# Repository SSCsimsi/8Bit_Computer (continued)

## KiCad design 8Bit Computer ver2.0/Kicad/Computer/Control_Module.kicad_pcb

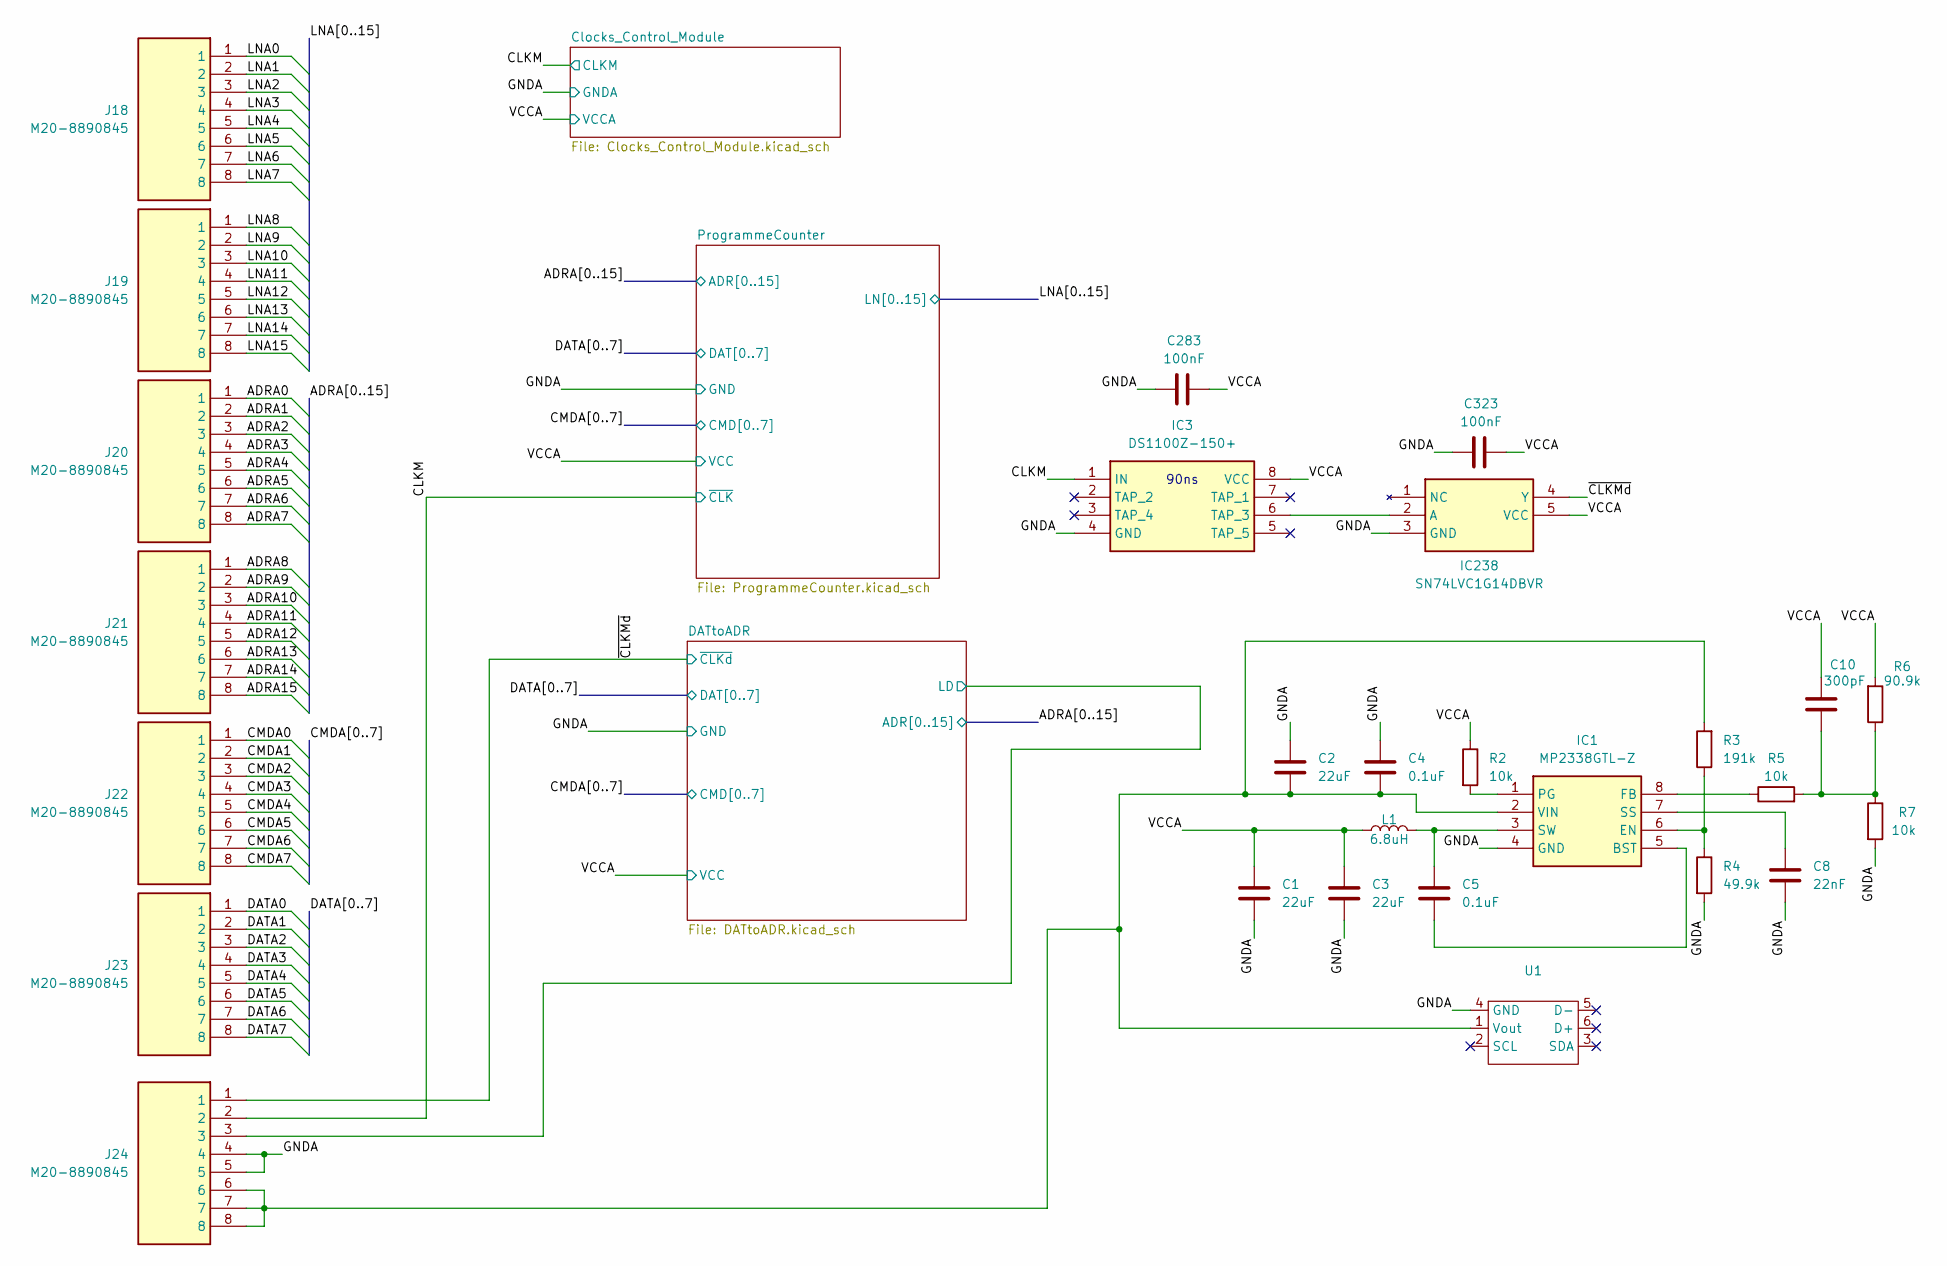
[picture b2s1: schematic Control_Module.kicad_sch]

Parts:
C1, C2, C3: 22uF; C_1206_3216Metric_Pad1.33x1.80mm_HandSolder
C4, C5: 0.1uF; C_1206_3216Metric_Pad1.33x1.80mm_HandSolder
C8: 22nF; C_1206_3216Metric_Pad1.33x1.80mm_HandSolder
C10: 300pF; C_1206_3216Metric_Pad1.33x1.80mm_HandSolder
C283, C323: 100nF; C_1206_3216Metric_Pad1.33x1.80mm_HandSolder
IC1: MP2338GTL-Z; MP2338GTLZ; Mouser Part Number 946-MP2338GTL-Z
IC3: DS1100Z-150+; SOIC127P600X175-8N; Mouser Part Number 700-DS1100Z-150
IC238: SN74LVC1G14DBVR; SOT95P280X145-5N; Mouser Part Number 595-SN74LVC1G14DBVR
J18, J19, J20, J21, J22, J23, J24: M20-8890845; M208890845; Mouser Part Number 855-M20-8890845
L1: 6.8uH; INDPM108100X400N; Mouser Part Number 80-MPEV1D1040L6R8
R2, R5, R7: 10k; R_1206_3216Metric_Pad1.30x1.75mm_HandSolder
R3: 191k; R_1206_3216Metric_Pad1.30x1.75mm_HandSolder
R4: 49.9k; R_1206_3216Metric_Pad1.30x1.75mm_HandSolder
R6: 90.9k; R_1206_3216Metric_Pad1.30x1.75mm_HandSolder
U1: USB_C_PD_Triggerboard

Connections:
/ADRA0: J20.1; also elsewhere on the board
/ADRA1: J20.2; also elsewhere on the board
/ADRA2: J20.3; also elsewhere on the board
/ADRA3: J20.4; also elsewhere on the board
/ADRA4: J20.5; also elsewhere on the board
/ADRA5: J20.6; also elsewhere on the board
/ADRA6: J20.7; also elsewhere on the board
/ADRA7: J20.8; also elsewhere on the board
/ADRA8: J21.1; also elsewhere on the board
/ADRA9: J21.2; also elsewhere on the board
/ADRA10: J21.3; also elsewhere on the board
/ADRA11: J21.4; also elsewhere on the board
/ADRA12: J21.5; also elsewhere on the board
/ADRA13: J21.6; also elsewhere on the board
/ADRA14: J21.7; also elsewhere on the board
/ADRA15: J21.8; also elsewhere on the board
/CMDA0: J22.1; also elsewhere on the board
/CMDA1: J22.2; also elsewhere on the board
/CMDA2: J22.3; also elsewhere on the board
/CMDA3: J22.4; also elsewhere on the board
/CMDA4: J22.5; also elsewhere on the board
/CMDA5: J22.6; also elsewhere on the board
/CMDA6: J22.7; also elsewhere on the board
/CMDA7: J22.8; also elsewhere on the board
/DATA0: J23.1; also elsewhere on the board
/DATA1: J23.2; also elsewhere on the board
/DATA2: J23.3; also elsewhere on the board
/DATA3: J23.4; also elsewhere on the board
/DATA4: J23.5; also elsewhere on the board
/DATA5: J23.6; also elsewhere on the board
/DATA6: J23.7; also elsewhere on the board
/DATA7: J23.8; also elsewhere on the board
/DATtoADR/LD: J24.3; also elsewhere on the board
/DATtoADR/~CLKd: IC3.6 (TAP_3), IC238.2 (A), IC238.4 (Y), J24.1; also elsewhere on the board
/GNDA: C1.2, C2.1, C3.2, C4.1, C8.2, C283.2, C323.2, IC1.4 (GND), IC3.4 (GND), IC238.3 (GND), J24.4, J24.5, R4.2, R7.2, U1.4 (GND); also elsewhere on the board
/LNA0: J18.1; also elsewhere on the board
/LNA1: J18.2; also elsewhere on the board
/LNA2: J18.3; also elsewhere on the board
/LNA3: J18.4; also elsewhere on the board
/LNA4: J18.5; also elsewhere on the board
/LNA5: J18.6; also elsewhere on the board
/LNA6: J18.7; also elsewhere on the board
/LNA7: J18.8; also elsewhere on the board
/LNA8: J19.1; also elsewhere on the board
/LNA9: J19.2; also elsewhere on the board
/LNA10: J19.3; also elsewhere on the board
/LNA11: J19.4; also elsewhere on the board
/LNA12: J19.5; also elsewhere on the board
/LNA13: J19.6; also elsewhere on the board
/LNA14: J19.7; also elsewhere on the board
/LNA15: J19.8; also elsewhere on the board
/ProgrammeCounter/~CLK: IC3.1 (IN), J24.2; also elsewhere on the board
/VCCA: C1.1, C3.1, C10.1, C283.1, C323.1, IC3.8 (VCC), IC238.5 (VCC), L1.1, R2.1, R6.2; also elsewhere on the board
unnamed: C10.2, R5.2, R6.1, R7.1
unnamed: C5.2, IC1.5 (BST)
unnamed: IC1.6 (EN), R3.1, R4.1
unnamed: IC1.8 (FB), R5.1
unnamed: IC1.1 (PG), R2.2
unnamed: C8.1, IC1.7 (SS)
unnamed: C5.1, IC1.3 (SW), L1.2
unnamed: C2.2, C4.2, IC1.2 (VIN), J24.6, J24.7, J24.8, R3.2, U1.1 (Vout)

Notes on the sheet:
90ns

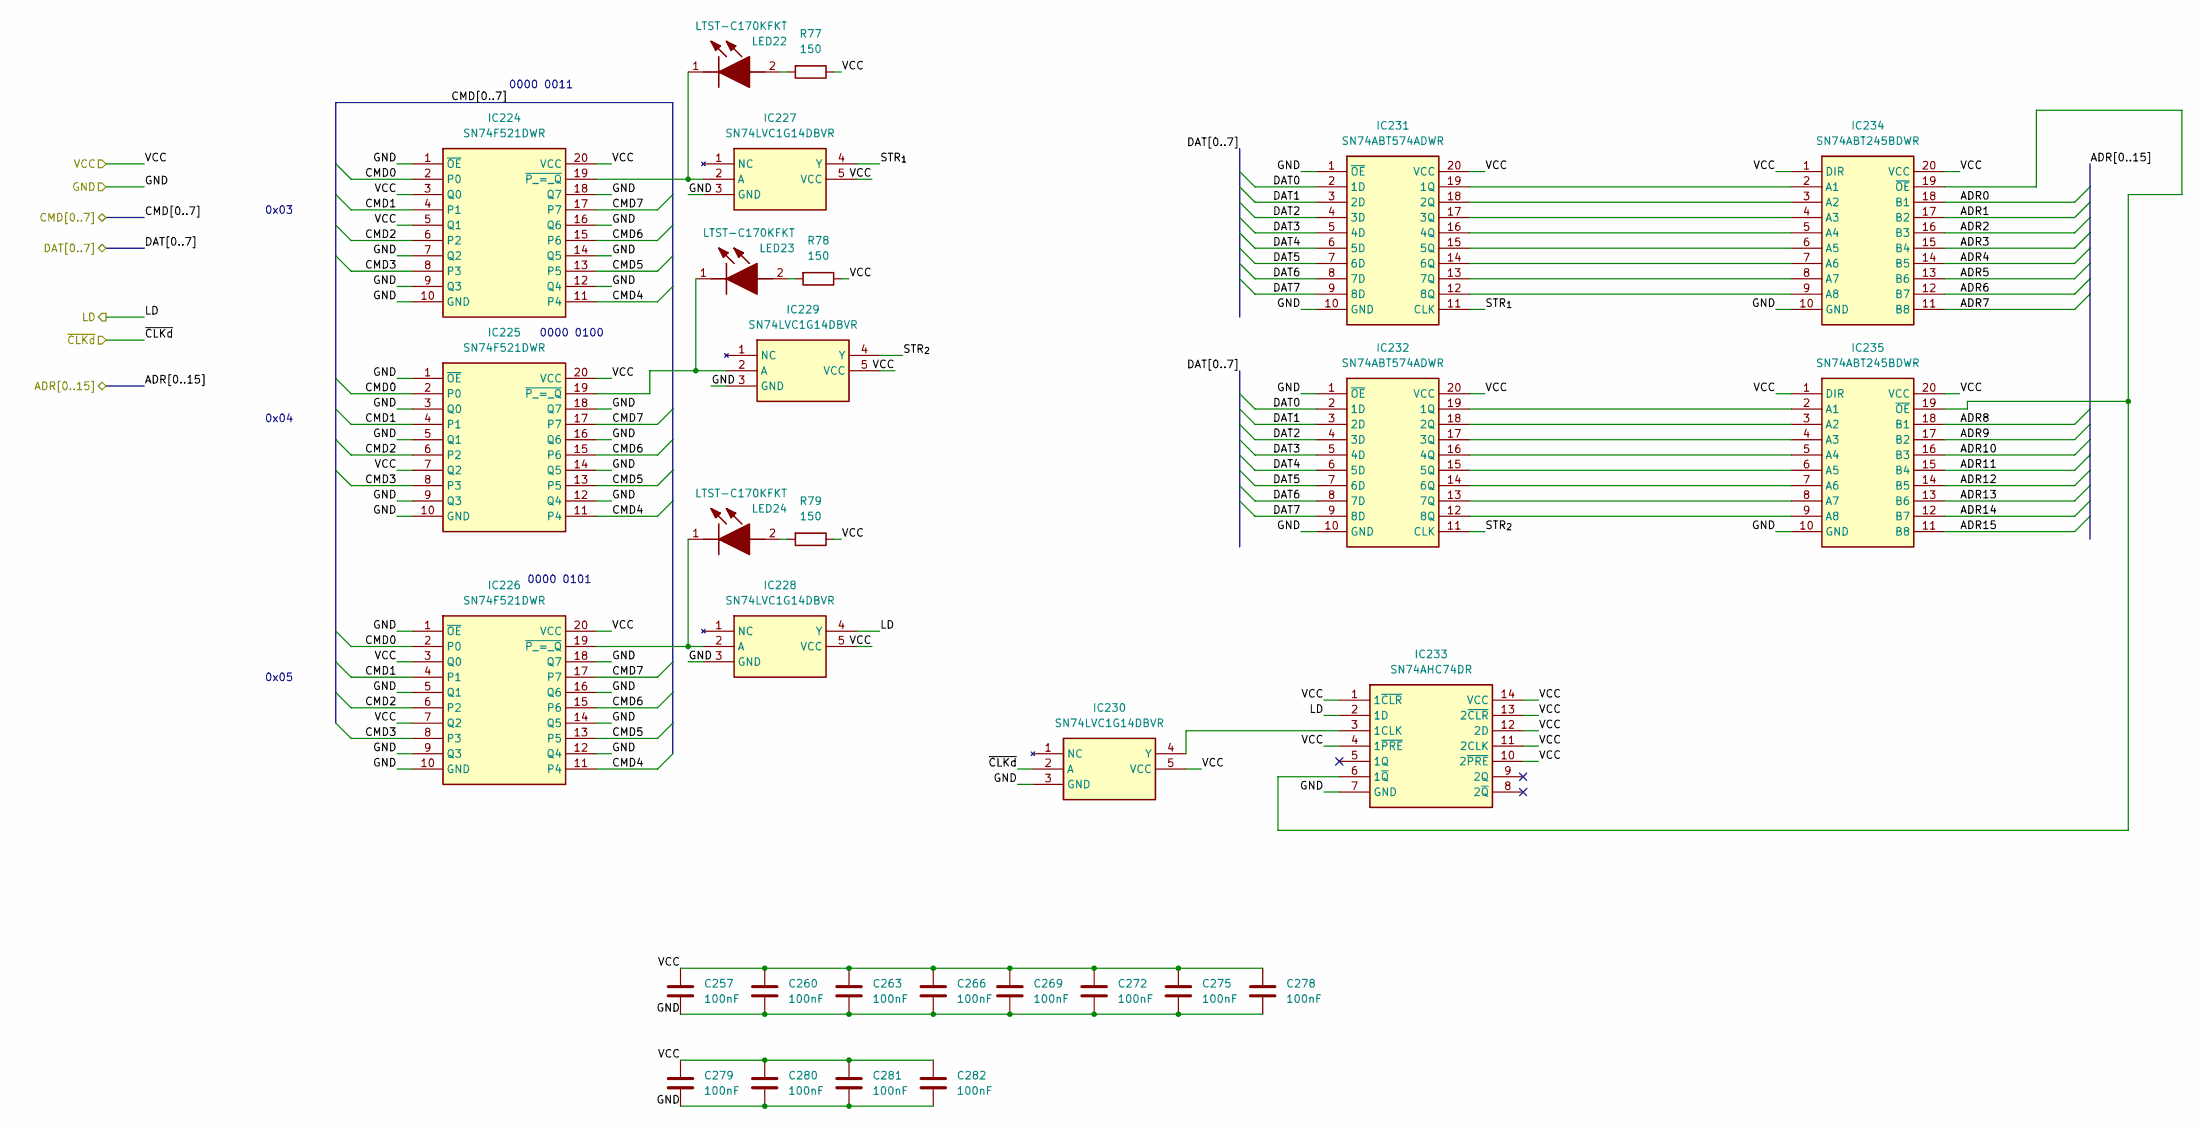
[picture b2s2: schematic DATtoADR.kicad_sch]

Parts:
C257, C260, C263, C266, C269, C272, C275, C278, C279, C280, C281, C282: 100nF; C_1206_3216Metric_Pad1.33x1.80mm_HandSolder
IC224, IC225, IC226: SN74F521DWR; SOIC127P1030X265-20N; Mouser Part Number 595-SN74F521DWR
IC227, IC228, IC229, IC230: SN74LVC1G14DBVR; SOT95P280X145-5N; Mouser Part Number 595-SN74LVC1G14DBVR
IC231, IC232: SN74ABT574ADWR; SOIC127P1030X265-20N; Mouser Part Number 595-SN74ABT574ADWR
IC233: SN74AHC74DR; SOIC127P600X175-14N; Mouser Part Number 595-SN74AHC74DR
IC234, IC235: SN74ABT245BDWR; SOIC127P1030X265-20N; Mouser Part Number 595-SN74ABT245BDWR
LED22, LED23, LED24: LTST-C170KFKT; LEDC2012X120N; Mouser Part Number 859-LTST-C170KFKT
R77, R78, R79: 150; R_1206_3216Metric_Pad1.30x1.75mm_HandSolder

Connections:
/ADRA0: IC234.18 (B1); also elsewhere on the board
/ADRA1: IC234.17 (B2); also elsewhere on the board
/ADRA2: IC234.16 (B3); also elsewhere on the board
/ADRA3: IC234.15 (B4); also elsewhere on the board
/ADRA4: IC234.14 (B5); also elsewhere on the board
/ADRA5: IC234.13 (B6); also elsewhere on the board
/ADRA6: IC234.12 (B7); also elsewhere on the board
/ADRA7: IC234.11 (B8); also elsewhere on the board
/ADRA8: IC235.18 (B1); also elsewhere on the board
/ADRA9: IC235.17 (B2); also elsewhere on the board
/ADRA10: IC235.16 (B3); also elsewhere on the board
/ADRA11: IC235.15 (B4); also elsewhere on the board
/ADRA12: IC235.14 (B5); also elsewhere on the board
/ADRA13: IC235.13 (B6); also elsewhere on the board
/ADRA14: IC235.12 (B7); also elsewhere on the board
/ADRA15: IC235.11 (B8); also elsewhere on the board
/CMDA0: IC224.2 (P0), IC225.2 (P0), IC226.2 (P0); also elsewhere on the board
/CMDA1: IC224.4 (P1), IC225.4 (P1), IC226.4 (P1); also elsewhere on the board
/CMDA2: IC224.6 (P2), IC225.6 (P2), IC226.6 (P2); also elsewhere on the board
/CMDA3: IC224.8 (P3), IC225.8 (P3), IC226.8 (P3); also elsewhere on the board
/CMDA4: IC224.11 (P4), IC225.11 (P4), IC226.11 (P4); also elsewhere on the board
/CMDA5: IC224.13 (P5), IC225.13 (P5), IC226.13 (P5); also elsewhere on the board
/CMDA6: IC224.15 (P6), IC225.15 (P6), IC226.15 (P6); also elsewhere on the board
/CMDA7: IC224.17 (P7), IC225.17 (P7), IC226.17 (P7); also elsewhere on the board
/DATA0: IC231.2 (1D), IC232.2 (1D); also elsewhere on the board
/DATA1: IC231.3 (2D), IC232.3 (2D); also elsewhere on the board
/DATA2: IC231.4 (3D), IC232.4 (3D); also elsewhere on the board
/DATA3: IC231.5 (4D), IC232.5 (4D); also elsewhere on the board
/DATA4: IC231.6 (5D), IC232.6 (5D); also elsewhere on the board
/DATA5: IC231.7 (6D), IC232.7 (6D); also elsewhere on the board
/DATA6: IC231.8 (7D), IC232.8 (7D); also elsewhere on the board
/DATA7: IC231.9 (8D), IC232.9 (8D); also elsewhere on the board
/DATtoADR/LD: IC228.4 (Y), IC233.2 (1D); also elsewhere on the board
/DATtoADR/STR_{1}: IC227.4 (Y), IC231.11 (CLK)
/DATtoADR/STR_{2}: IC229.4 (Y), IC232.11 (CLK)
/DATtoADR/~CLKd: IC230.2 (A); also elsewhere on the board
/GNDA: C257.1, C260.1, C263.1, C266.1, C269.1, C272.1, C275.1, C278.1, C279.1, C280.1, C281.1, C282.1, IC224.1 (~OE), IC224.7 (Q2), IC224.9 (Q3), IC224.10 (GND), IC224.12 (Q4), IC224.14 (Q5), IC224.16 (Q6), IC224.18 (Q7), IC225.1 (~OE), IC225.3 (Q0), IC225.5 (Q1), IC225.9 (Q3), IC225.10 (GND), IC225.12 (Q4), IC225.14 (Q5), IC225.16 (Q6), IC225.18 (Q7), IC226.1 (~OE), IC226.5 (Q1), IC226.9 (Q3), IC226.10 (GND), IC226.12 (Q4), IC226.14 (Q5), IC226.16 (Q6), IC226.18 (Q7), IC227.3 (GND), IC228.3 (GND), IC229.3 (GND), IC230.3 (GND), IC231.1 (~OE), IC231.10 (GND), IC232.1 (~OE), IC232.10 (GND), IC233.7 (GND), IC234.10 (GND), IC235.10 (GND); also elsewhere on the board
/VCCA: C257.2, C260.2, C263.2, C266.2, C269.2, C272.2, C275.2, C278.2, C279.2, C280.2, C281.2, C282.2, IC224.3 (Q0), IC224.5 (Q1), IC224.20 (VCC), IC225.7 (Q2), IC225.20 (VCC), IC226.3 (Q0), IC226.7 (Q2), IC226.20 (VCC), IC227.5 (VCC), IC228.5 (VCC), IC229.5 (VCC), IC230.5 (VCC), IC231.20 (VCC), IC232.20 (VCC), IC233.1 (1~CLR), IC233.4 (1~PRE), IC233.10 (2~PRE), IC233.11 (2CLK), IC233.12 (2D), IC233.13 (2~CLR), IC233.14 (VCC), IC234.1 (DIR), IC234.20 (VCC), IC235.1 (DIR), IC235.20 (VCC), R77.1, R78.1, R79.1; also elsewhere on the board
unnamed: IC224.19 (~P_=_Q), IC227.2 (A), LED22.1 (K)
unnamed: IC225.19 (~P_=_Q), IC229.2 (A), LED23.1 (K)
unnamed: IC226.19 (~P_=_Q), IC228.2 (A), LED24.1 (K)
unnamed: IC230.4 (Y), IC233.3 (1CLK)
unnamed: IC231.19 (1Q), IC234.2 (A1)
unnamed: IC231.18 (2Q), IC234.3 (A2)
unnamed: IC231.17 (3Q), IC234.4 (A3)
unnamed: IC231.16 (4Q), IC234.5 (A4)
unnamed: IC231.15 (5Q), IC234.6 (A5)
unnamed: IC231.14 (6Q), IC234.7 (A6)
unnamed: IC231.13 (7Q), IC234.8 (A7)
unnamed: IC231.12 (8Q), IC234.9 (A8)
unnamed: IC232.19 (1Q), IC235.2 (A1)
unnamed: IC232.18 (2Q), IC235.3 (A2)
unnamed: IC232.17 (3Q), IC235.4 (A3)
unnamed: IC232.16 (4Q), IC235.5 (A4)
unnamed: IC232.15 (5Q), IC235.6 (A5)
unnamed: IC232.14 (6Q), IC235.7 (A6)
unnamed: IC232.13 (7Q), IC235.8 (A7)
unnamed: IC232.12 (8Q), IC235.9 (A8)
unnamed: IC233.6 (1~Q), IC234.19 (~OE), IC235.19 (~OE)
unnamed: LED22.2 (A), R77.2
unnamed: LED23.2 (A), R78.2
unnamed: LED24.2 (A), R79.2

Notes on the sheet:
0000 0011
0000 0100
0x04
0x05
0000 0101
0x03

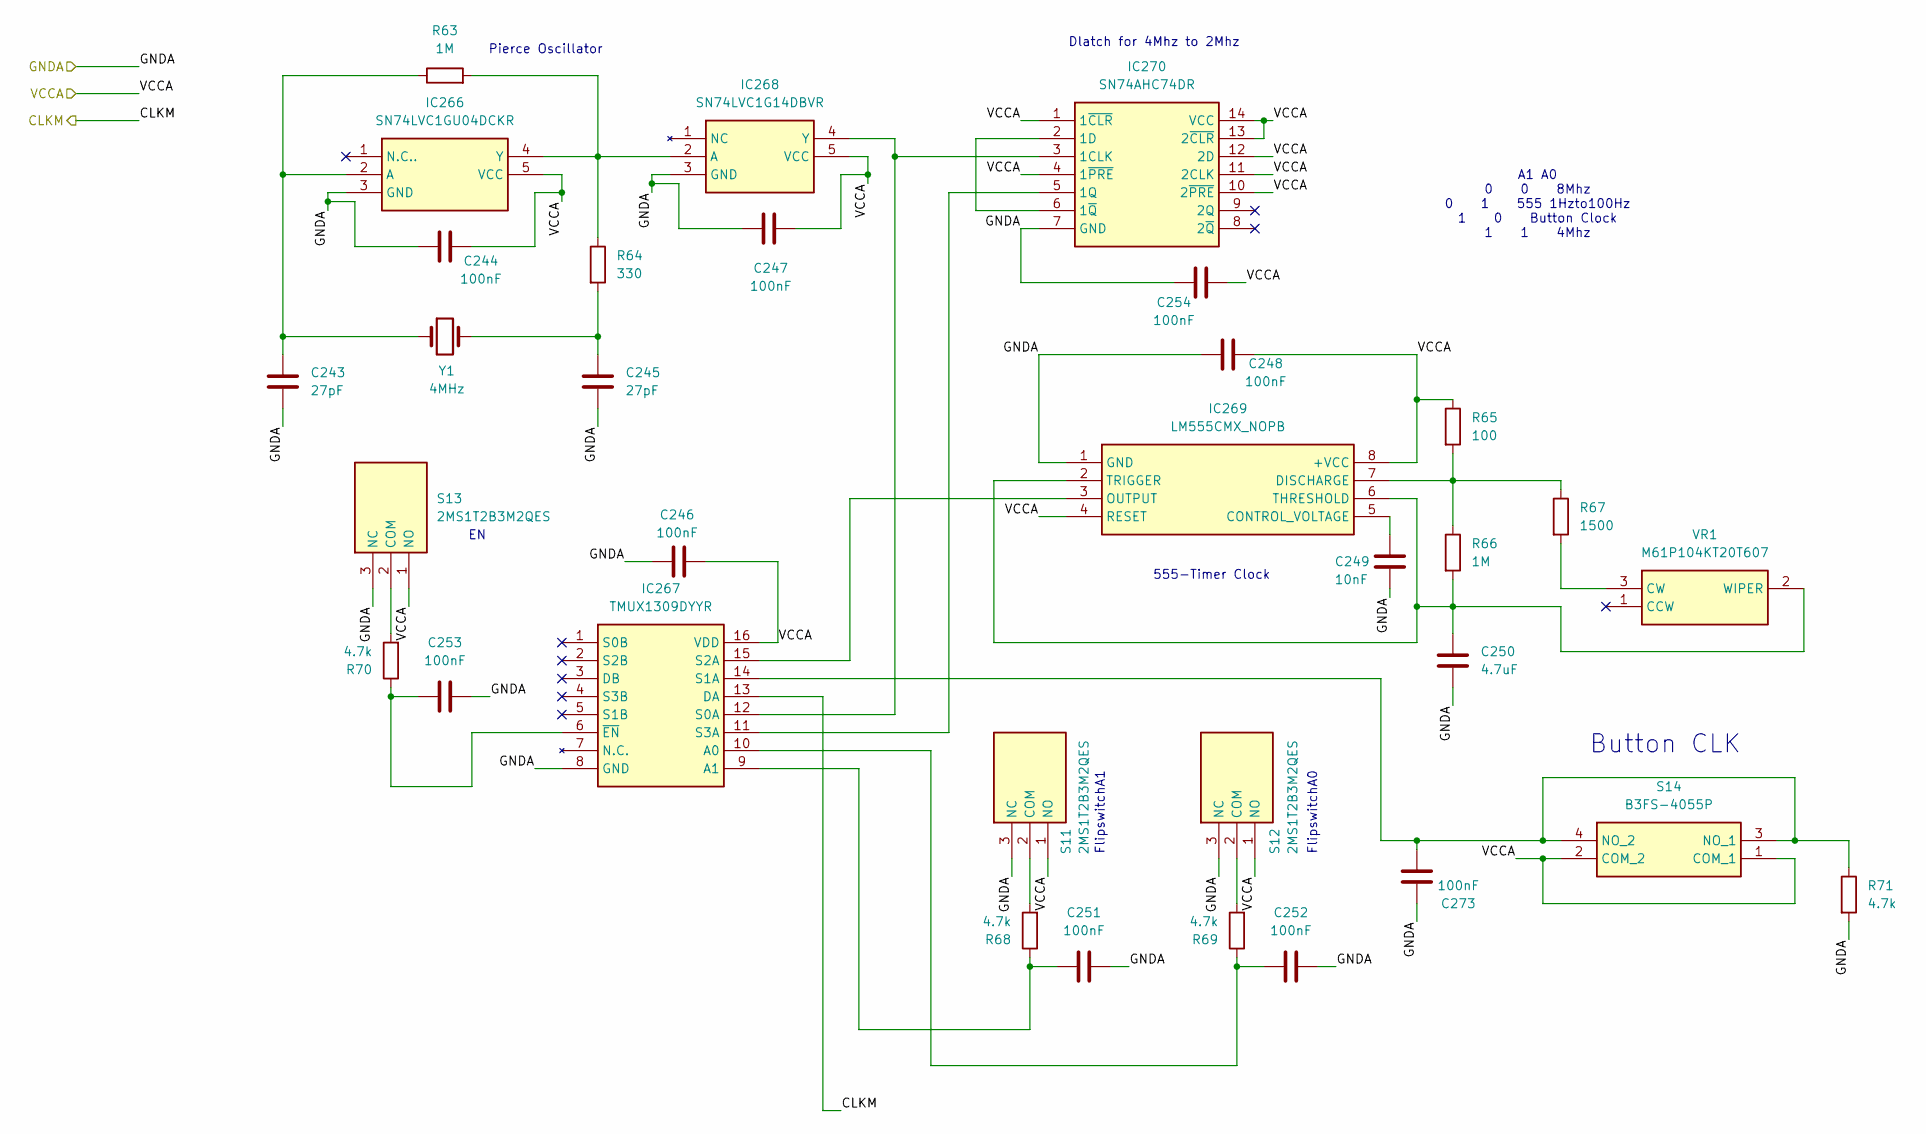
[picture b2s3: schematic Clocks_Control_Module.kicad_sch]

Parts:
C243, C245: 27pF; C_1206_3216Metric_Pad1.33x1.80mm_HandSolder
C244, C246, C247, C248, C251, C252, C253, C254, C273: 100nF; C_1206_3216Metric_Pad1.33x1.80mm_HandSolder
C249: 10nF; C_1206_3216Metric_Pad1.33x1.80mm_HandSolder
C250: 4.7uF; C_1206_3216Metric_Pad1.33x1.80mm_HandSolder
IC266: SN74LVC1GU04DCKR; SOT65P210X110-5N; Mouser Part Number 595-SN74LVC1GU04DCKR
IC267: TMUX1309DYYR; SOP50P326X110-16N; Mouser Part Number 595-TMUX1309DYYR
IC268: SN74LVC1G14DBVR; SOT95P280X145-5N; Mouser Part Number 595-SN74LVC1G14DBVR
IC269: LM555CMX_NOPB; SOIC127P600X175-8N; Mouser Part Number 926-LM555CMX/NOPB
IC270: SN74AHC74DR; SOIC127P600X175-14N; Mouser Part Number 595-SN74AHC74DR
R63, R66: 1M; R_1206_3216Metric_Pad1.30x1.75mm_HandSolder
R64: 330; R_1206_3216Metric_Pad1.30x1.75mm_HandSolder
R65: 100; R_1206_3216Metric_Pad1.30x1.75mm_HandSolder
R67: 1500; R_1206_3216Metric_Pad1.30x1.75mm_HandSolder
R68, R69, R70, R71: 4.7k; R_1206_3216Metric_Pad1.30x1.75mm_HandSolder
S11, S12, S13: 2MS1T2B3M2QES; Mouser Part Number 118-2MS1T2B3M2QES
S14: B3FS-4055P; B3FS4055P; Mouser Part Number 653-B3FS-4055P
VR1: M61P104KT20T607; Manufacturer_Part_Number M61P104KT20T607
Y1: 4MHz; Crystal_SMD_HC49-SD_HandSoldering

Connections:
/GNDA: C243.2, C244.2, C245.2, C246.2, C247.2, C248.2, C249.2, C250.2, C251.1, C252.1, C253.1, C254.2, C273.1, IC266.3 (GND), IC267.8 (GND), IC268.3 (GND), IC269.1 (GND), IC270.7 (GND), R71.2, S11.3 (NC), S12.3 (NC), S13.3 (NC); also elsewhere on the board
/ProgrammeCounter/~CLK: IC267.13 (DA); also elsewhere on the board
/VCCA: C244.1, C246.1, C247.1, C248.1, C254.1, IC266.5 (VCC), IC267.16 (VDD), IC268.5 (VCC), IC269.4 (RESET), IC269.8 (+VCC), IC270.1 (1~CLR), IC270.4 (1~PRE), IC270.10 (2~PRE), IC270.11 (2CLK), IC270.12 (2D), IC270.13 (2~CLR), IC270.14 (VCC), R65.1, S11.1 (NO), S12.1 (NO), S13.1 (NO), S14.1 (COM_1), S14.2 (COM_2); also elsewhere on the board
unnamed: C245.1, R64.2, Y1.2
unnamed: C243.1, IC266.2 (A), R63.1, Y1.1
unnamed: IC266.4 (Y), IC268.2 (A), R63.2, R64.1
unnamed: C252.2, IC267.10 (A0), R69.1
unnamed: C251.2, IC267.9 (A1), R68.1
unnamed: IC267.12 (S0A), IC268.4 (Y), IC270.3 (1CLK)
unnamed: C273.2, IC267.14 (S1A), R71.1, S14.3 (NO_1), S14.4 (NO_2)
unnamed: IC267.15 (S2A), IC269.3 (OUTPUT)
unnamed: IC267.11 (S3A), IC270.5 (1Q)
unnamed: C253.2, IC267.6 (~EN), R70.1
unnamed: C249.1, IC269.5 (CONTROL_VOLTAGE)
unnamed: IC269.7 (DISCHARGE), R65.2, R66.1, R67.1
unnamed: C250.1, IC269.2 (TRIGGER), IC269.6 (THRESHOLD), R66.2, VR1.2 (WIPER)
unnamed: IC270.2 (1D), IC270.6 (1~Q)
unnamed: R68.2, S11.2 (COM)
unnamed: R69.2, S12.2 (COM)
unnamed: R70.2, S13.2 (COM)
unnamed: R67.2, VR1.3 (CW)

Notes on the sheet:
Pierce Oscillator
Dlatch for 4Mhz to 2Mhz
555-Timer Clock
A1 A0 0 0 8Mhz 0 1 555 1Hzto100Hz 1 0 Button Clock 1 1 4Mhz
FlipswitchA1
Button CLK
FlipswitchA0

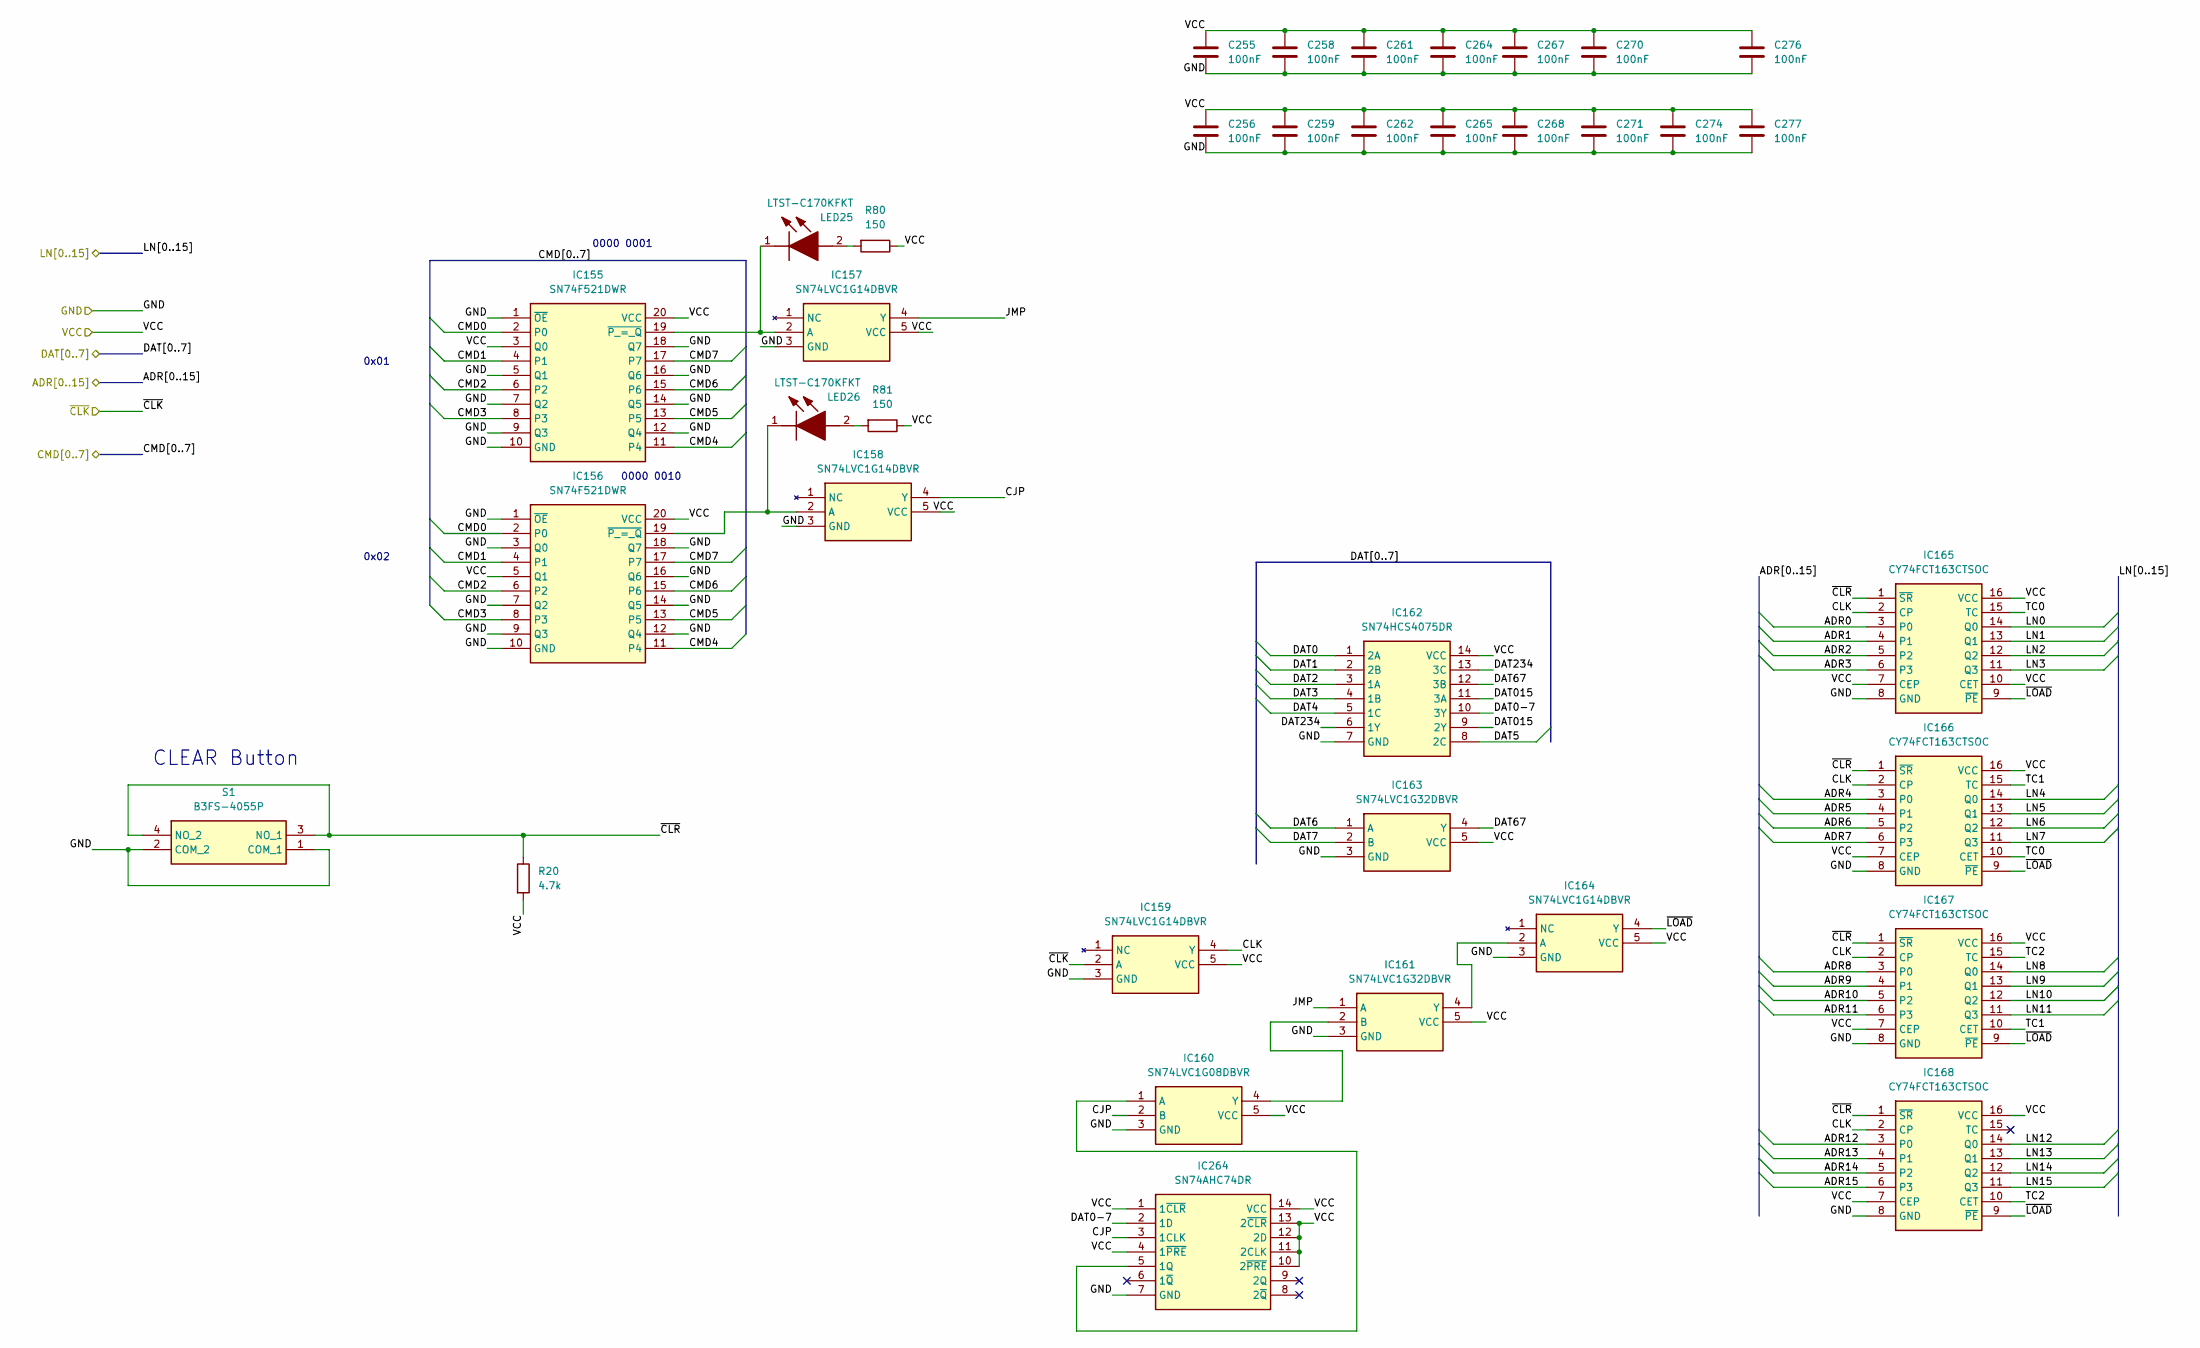
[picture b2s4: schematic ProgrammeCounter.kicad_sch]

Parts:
C255, C256, C258, C259, C261, C262, C264, C265, C267, C268, C270, C271, C274, C276, C277: 100nF; C_1206_3216Metric_Pad1.33x1.80mm_HandSolder
IC155, IC156: SN74F521DWR; SOIC127P1030X265-20N; Mouser Part Number 595-SN74F521DWR
IC157, IC158, IC159, IC164: SN74LVC1G14DBVR; SOT95P280X145-5N; Mouser Part Number 595-SN74LVC1G14DBVR
IC160: SN74LVC1G08DBVR; SOT95P280X145-5N; Mouser Part Number 595-SN74LVC1G08DBVR
IC161, IC163: SN74LVC1G32DBVR; SOT95P280X145-5N; Mouser Part Number 595-SN74LVC1G32DBVR
IC162: SN74HCS4075DR; SOIC127P600X175-14N; Mouser Part Number 595-SN74HCS4075DR
IC165, IC166, IC167, IC168: CY74FCT163CTSOC; SOIC127P1030X265-16N; Mouser Part Number 595-CY74FCT163CTSOC
IC264: SN74AHC74DR; SOIC127P600X175-14N; Mouser Part Number 595-SN74AHC74DR
LED25, LED26: LTST-C170KFKT; LEDC2012X120N; Mouser Part Number 859-LTST-C170KFKT
R20: 4.7k; R_1206_3216Metric_Pad1.30x1.75mm_HandSolder
R80, R81: 150; R_1206_3216Metric_Pad1.30x1.75mm_HandSolder
S1: B3FS-4055P; B3FS4055P; Mouser Part Number 653-B3FS-4055P

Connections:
/ADRA0: IC165.3 (P0); also elsewhere on the board
/ADRA1: IC165.4 (P1); also elsewhere on the board
/ADRA2: IC165.5 (P2); also elsewhere on the board
/ADRA3: IC165.6 (P3); also elsewhere on the board
/ADRA4: IC166.3 (P0); also elsewhere on the board
/ADRA5: IC166.4 (P1); also elsewhere on the board
/ADRA6: IC166.5 (P2); also elsewhere on the board
/ADRA7: IC166.6 (P3); also elsewhere on the board
/ADRA8: IC167.3 (P0); also elsewhere on the board
/ADRA9: IC167.4 (P1); also elsewhere on the board
/ADRA10: IC167.5 (P2); also elsewhere on the board
/ADRA11: IC167.6 (P3); also elsewhere on the board
/ADRA12: IC168.3 (P0); also elsewhere on the board
/ADRA13: IC168.4 (P1); also elsewhere on the board
/ADRA14: IC168.5 (P2); also elsewhere on the board
/ADRA15: IC168.6 (P3); also elsewhere on the board
/CMDA0: IC155.2 (P0), IC156.2 (P0); also elsewhere on the board
/CMDA1: IC155.4 (P1), IC156.4 (P1); also elsewhere on the board
/CMDA2: IC155.6 (P2), IC156.6 (P2); also elsewhere on the board
/CMDA3: IC155.8 (P3), IC156.8 (P3); also elsewhere on the board
/CMDA4: IC155.11 (P4), IC156.11 (P4); also elsewhere on the board
/CMDA5: IC155.13 (P5), IC156.13 (P5); also elsewhere on the board
/CMDA6: IC155.15 (P6), IC156.15 (P6); also elsewhere on the board
/CMDA7: IC155.17 (P7), IC156.17 (P7); also elsewhere on the board
/DATA0: IC162.1 (2A); also elsewhere on the board
/DATA1: IC162.2 (2B); also elsewhere on the board
/DATA2: IC162.3 (1A); also elsewhere on the board
/DATA3: IC162.4 (1B); also elsewhere on the board
/DATA4: IC162.5 (1C); also elsewhere on the board
/DATA5: IC162.8 (2C); also elsewhere on the board
/DATA6: IC163.1 (A); also elsewhere on the board
/DATA7: IC163.2 (B); also elsewhere on the board
/GNDA: C255.1, C256.1, C258.1, C259.1, C261.1, C262.1, C264.1, C265.1, C267.1, C268.1, C270.1, C271.1, C274.1, C276.1, C277.1, IC155.1 (~OE), IC155.5 (Q1), IC155.7 (Q2), IC155.9 (Q3), IC155.10 (GND), IC155.12 (Q4), IC155.14 (Q5), IC155.16 (Q6), IC155.18 (Q7), IC156.1 (~OE), IC156.3 (Q0), IC156.7 (Q2), IC156.9 (Q3), IC156.10 (GND), IC156.12 (Q4), IC156.14 (Q5), IC156.16 (Q6), IC156.18 (Q7), IC157.3 (GND), IC158.3 (GND), IC159.3 (GND), IC160.3 (GND), IC161.3 (GND), IC162.7 (GND), IC163.3 (GND), IC164.3 (GND), IC165.8 (GND), IC166.8 (GND), IC167.8 (GND), IC168.8 (GND), IC264.7 (GND), S1.1 (COM_1), S1.2 (COM_2); also elsewhere on the board
/LNA0: IC165.14 (Q0); also elsewhere on the board
/LNA1: IC165.13 (Q1); also elsewhere on the board
/LNA2: IC165.12 (Q2); also elsewhere on the board
/LNA3: IC165.11 (Q3); also elsewhere on the board
/LNA4: IC166.14 (Q0); also elsewhere on the board
/LNA5: IC166.13 (Q1); also elsewhere on the board
/LNA6: IC166.12 (Q2); also elsewhere on the board
/LNA7: IC166.11 (Q3); also elsewhere on the board
/LNA8: IC167.14 (Q0); also elsewhere on the board
/LNA9: IC167.13 (Q1); also elsewhere on the board
/LNA10: IC167.12 (Q2); also elsewhere on the board
/LNA11: IC167.11 (Q3); also elsewhere on the board
/LNA12: IC168.14 (Q0); also elsewhere on the board
/LNA13: IC168.13 (Q1); also elsewhere on the board
/LNA14: IC168.12 (Q2); also elsewhere on the board
/LNA15: IC168.11 (Q3); also elsewhere on the board
/ProgrammeCounter/CJP: IC158.4 (Y), IC160.2 (B), IC264.3 (1CLK)
/ProgrammeCounter/CLK: IC159.4 (Y), IC165.2 (CP), IC166.2 (CP), IC167.2 (CP), IC168.2 (CP)
/ProgrammeCounter/DAT0-7: IC162.10 (3Y), IC264.2 (1D)
/ProgrammeCounter/DAT015: IC162.9 (2Y), IC162.11 (3A)
/ProgrammeCounter/DAT67: IC162.12 (3B), IC163.4 (Y)
/ProgrammeCounter/DAT234: IC162.6 (1Y), IC162.13 (3C)
/ProgrammeCounter/JMP: IC157.4 (Y), IC161.1 (A)
/ProgrammeCounter/TC0: IC165.15 (TC), IC166.10 (CET)
/ProgrammeCounter/TC1: IC166.15 (TC), IC167.10 (CET)
/ProgrammeCounter/TC2: IC167.15 (TC), IC168.10 (CET)
/ProgrammeCounter/~CLK: IC159.2 (A); also elsewhere on the board
/ProgrammeCounter/~CLR: IC165.1 (~SR), IC166.1 (~SR), IC167.1 (~SR), IC168.1 (~SR), R20.1, S1.3 (NO_1), S1.4 (NO_2)
/ProgrammeCounter/~LOAD: IC164.4 (Y), IC165.9 (~PE), IC166.9 (~PE), IC167.9 (~PE), IC168.9 (~PE)
/VCCA: C255.2, C256.2, C258.2, C259.2, C261.2, C262.2, C264.2, C265.2, C267.2, C268.2, C270.2, C271.2, C274.2, C276.2, C277.2, IC155.3 (Q0), IC155.20 (VCC), IC156.5 (Q1), IC156.20 (VCC), IC157.5 (VCC), IC158.5 (VCC), IC159.5 (VCC), IC160.5 (VCC), IC161.5 (VCC), IC162.14 (VCC), IC163.5 (VCC), IC164.5 (VCC), IC165.7 (CEP), IC165.10 (CET), IC165.16 (VCC), IC166.7 (CEP), IC166.16 (VCC), IC167.7 (CEP), IC167.16 (VCC), IC168.7 (CEP), IC168.16 (VCC), IC264.1 (1~CLR), IC264.4 (1~PRE), IC264.10 (2~PRE), IC264.11 (2CLK), IC264.12 (2D), IC264.13 (2~CLR), IC264.14 (VCC), R20.2, R80.1, R81.1; also elsewhere on the board
unnamed: IC155.19 (~P_=_Q), IC157.2 (A), LED25.1 (K)
unnamed: IC156.19 (~P_=_Q), IC158.2 (A), LED26.1 (K)
unnamed: IC160.1 (A), IC264.5 (1Q)
unnamed: IC160.4 (Y), IC161.2 (B)
unnamed: IC161.4 (Y), IC164.2 (A)
unnamed: LED25.2 (A), R80.2
unnamed: LED26.2 (A), R81.2

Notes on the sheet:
0000 0010
0000 0001
0x01
0x02
CLEAR Button

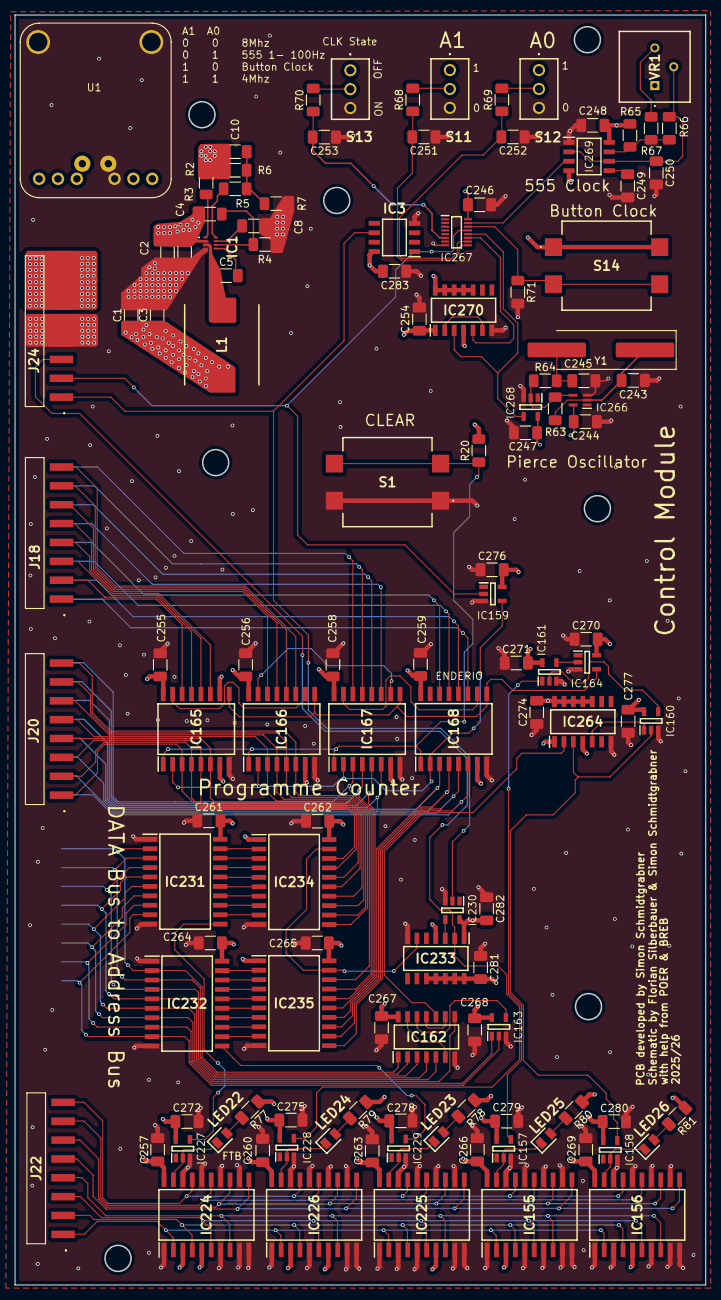
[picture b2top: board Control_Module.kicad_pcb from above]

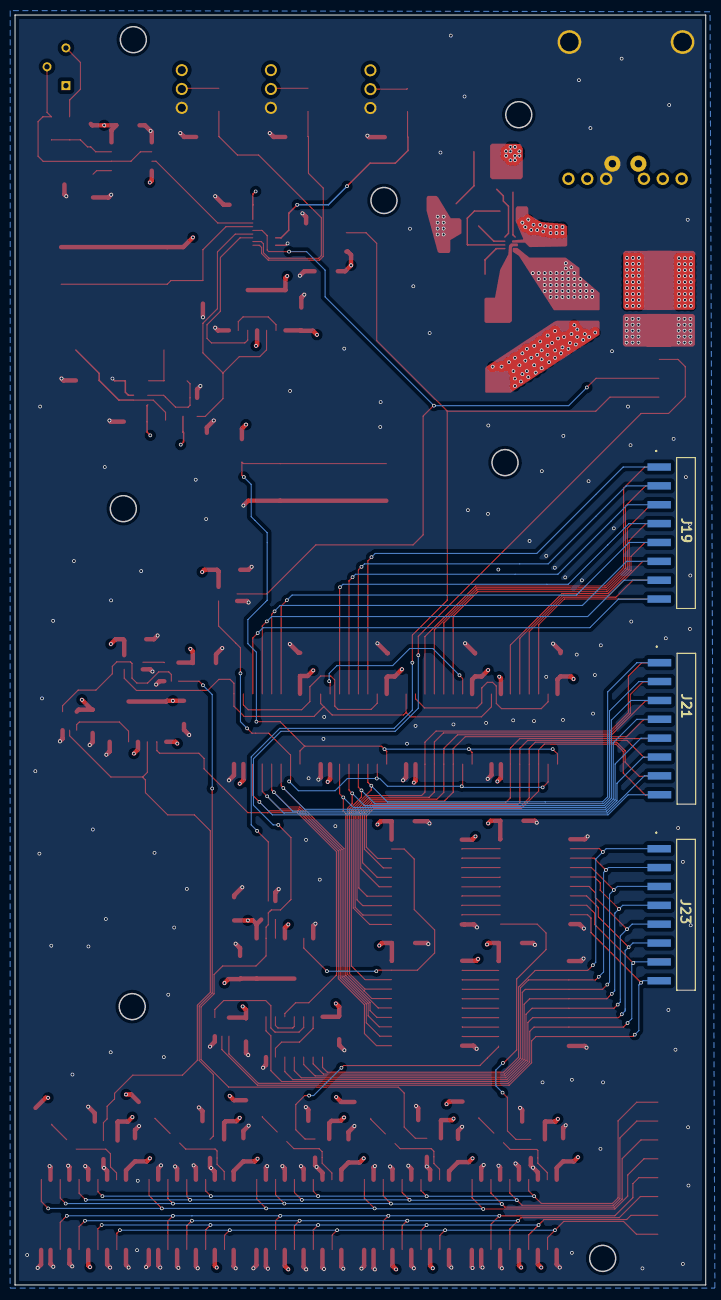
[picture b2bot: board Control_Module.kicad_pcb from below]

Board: 4 copper layers, 93.0 x 171.0 mm, 123 parts (3 on the bottom side), 124 nets.
